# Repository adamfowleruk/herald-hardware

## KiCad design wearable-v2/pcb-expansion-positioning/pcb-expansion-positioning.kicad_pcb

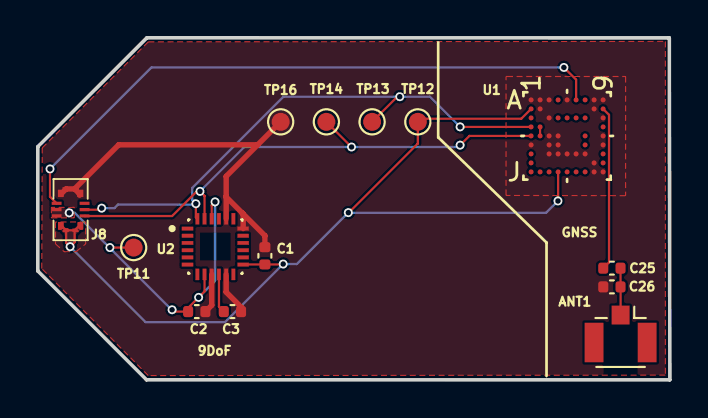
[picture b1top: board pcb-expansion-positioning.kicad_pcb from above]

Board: 2 copper layers, 35.1 x 19.0 mm, 14 parts (0 on the bottom side), 10 nets.

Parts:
ANT1: U.FL_Hirose_U.FL-R-SMT-1_Vertical
C1, C2, C3: 100nF; C_0402_1005Metric
C25: 120pF; C_0402_1005Metric
C26: Tune (~120pF); C_0402_1005Metric
J8: HERALD_V2_CONN_PLUG; HERALD_V2_CONN_PORT
TP11: VDD1; TestPoint_Pad_D1.0mm
TP12: VDD; TestPoint_Pad_D1.0mm
TP13: SDA; TestPoint_Pad_D1.0mm
TP14: SCL; TestPoint_Pad_D1.0mm
TP16: GND; TestPoint_Pad_D1.0mm
U1: MIA-M10Q-00B; LGA_M10Q-00B_UBL
U2: ICM-20948; ICM-20948-QFN40P300X300X105-24N

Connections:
/Positioning Board V1/ANT_RF: C25.1, U1.B9 (RF_IN)
/Positioning Board V1/GNSS_INT: J8.6 (INT), U1.A6 (EXTINT)
/Positioning Board V1/SCL: J8.3 (SCL), TP14.1, U1.E1 (SCL), U2.23 (SCL/SCLK)
/Positioning Board V1/SDA: J8.5 (SDA), TP13.1, U1.D1 (SDA), U2.24 (SDA/SDI)
GND: C1.2, C2.1, C3.1, C26.2, J8.8 (GND), TP16.1, U1.A1 (GND), U1.A2 (GND), U1.A3 (GND), U1.A5 (RTC_O), U1.A8 (GND), U1.A9 (GND), U1.B2 (GND), U1.B8 (GND), U1.C3 (GND), U1.C9 (GND), U1.E3 (GND), U1.E4 (GND), U1.E9 (GND), U1.F1 (GND), U1.F3 (GND), U1.F4 (GND), U1.F9 (RESERVED), U1.G3 (GND), U1.G4 (GND), U1.G5 (GND), U1.G6 (GND), U1.G7 (RESERVED), U1.H8 (GND), U1.J8 (GND), U1.J9 (GND), U2.9 (AD0/SDO), U2.11 (FSYNC), U2.18 (GND), U2.20 (RESV_20)
unnamed: ANT1.1, C25.2, C26.1
unnamed: U1.D2 (RESERVED), U1.E2 (RESERVED)
unnamed: C3.2, U2.10 (REGOUT)
VDD: C1.1, J8.1 (3V3), TP12.1, U1.B1 (VCC), U1.J4 (V_IO), U2.13 (VDD)
VDD1: C2.2, J8.2 (1V8), J8.4 (1V8), TP11.1, U2.8 (VDDIO), U2.22 (~CS)

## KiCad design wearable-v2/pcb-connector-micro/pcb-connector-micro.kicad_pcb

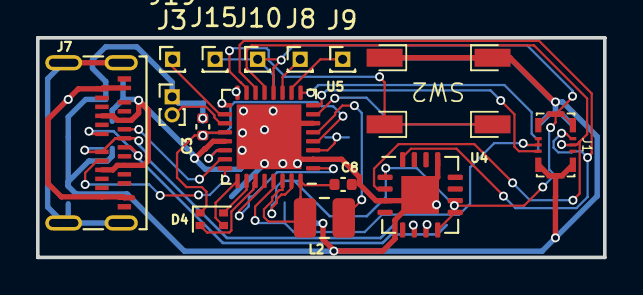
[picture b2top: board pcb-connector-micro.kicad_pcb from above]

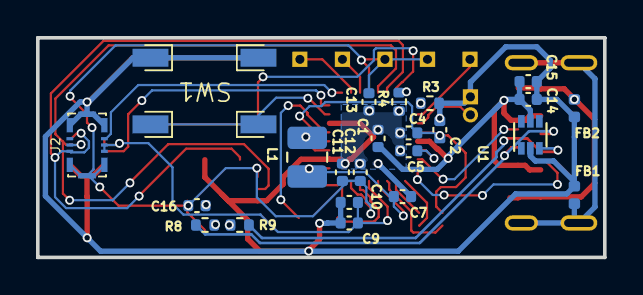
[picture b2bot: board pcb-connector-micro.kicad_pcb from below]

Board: 2 copper layers, 31.5 x 12.2 mm, 38 parts (23 on the bottom side), 33 nets.

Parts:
C1, C5: 1uF; C_0402_1005Metric
C2, C3, C4, C7, C8, C9, C10, C11, C12: 10uF; C_0402_1005Metric
C13, C16: 100nF; C_0402_1005Metric
C14: 4.7uF; C_0402_1005Metric
C15: 100nF/100V; C_0402_1005Metric
D4: LED_ARGY; LED_Kingbright_APHF1608
FB1, FB2: 120R/0.6A; L_0402_1005Metric
J1, J2: HERALD_V2_CONN_RECEPTACLE
J3, J8, J9, J10, J15: Conn_01x01_Pin; PinHeader_1x01_P1.00mm_Vertical
J7: USB_C_Receptacle_USB2.0; USB_C_Receptacle_IPxx
J19: Conn_01x02_Pin; PinHeader_1x02_P1.00mm_Vertical
L1, L2: 2.2uH; L_1008_2520Metric
R3: 4.7K; R_0402_1005Metric
R4: 499K; R_0402_1005Metric
R8, R9: 27; R_0402_1005Metric
SW1, SW2: PTS526
U1: DT1446-04V; SOT-563
U4: FT201XQ; QFN-16-1EP_4x4mm_P0.65mm_EP2.1x2.1mm
U5: nPM1300-QEAA; QFN-32-1EP_5x5mm_P0.5mm_EP3.6x3.6mm

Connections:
/Micro Connector/+BATT: J19.2, U5.19 (VBAT)
/Micro Connector/CC1: J7.A5 (CC1), U5.23 (CC1)
/Micro Connector/CC2: J7.B5 (CC2), U5.24 (CC2)
/Micro Connector/GPIO_1: J9.1, U5.10 (GPIO3)
/Micro Connector/GPIO_2: J8.1, U5.11 (GPIO4)
/Micro Connector/I3C_SCL: J1.3 (SCL), J2.3 (SCL), U4.16 (SCL), U5.14 (SCL)
/Micro Connector/I3C_SDA: J1.5 (SDA), J2.5 (SDA), U4.2 (SDA), U5.13 (SDA)
/Micro Connector/INT_1: J1.6 (INT), U5.8 (GPIO1)
/Micro Connector/INT_2: J2.6 (INT), U5.9 (GPIO2)
/Micro Connector/LED_PWR_G: D4.3 (GK), U5.25 (LED0)
/Micro Connector/LED_PWR_R: D4.2 (RK), U5.27 (LED2)
/Micro Connector/LED_PWR_Y: D4.4 (BK), U5.26 (LED1)
/Micro Connector/NTC: J3.1, U5.18 (NTC)
/Micro Connector/RST_CONN: SW1.1, SW1.2, U5.7 (GPIO0)
/Micro Connector/USB_D+: J7.A6 (D+), J7.B6 (D+), R9.1, U1.3
/Micro Connector/USB_D-: J7.A7 (D-), J7.B7 (D-), R8.2, U1.1
/Micro Connector/VBUSOUT: C5.1, U5.22 (VBUSOUT)
/Micro Connector/VCC_1V8: C9.1, C10.1, J1.2 (1V8), J1.4 (1V8), J2.2 (1V8), J2.4 (1V8), U5.29 (VOUTLDO1)
/Micro Connector/VOUT1: C7.1, L1.1, U5.1 (VOUT1), U5.28 (VINLDO1)
/Micro Connector/VOUT2: C8.1, L2.1, U5.30 (VINLDO2), U5.32 (VOUT2)
/Micro Connector/VSYS: C2.1, C3.1, C4.1, D4.1 (A), U5.4 (PVDD), U5.20 (VSYS)
Earth: FB1.1, J7.S1 (SHIELD)
GND: C1.2, C2.2, C3.2, C4.2, C5.2, C7.2, C8.2, C9.2, C10.2, C11.2, C12.2, C13.1, C14.1, C15.1, C16.2, FB1.2, FB2.2, J1.8 (GND), J2.8 (GND), J19.1, R3.2, R4.1, SW1.3, SW1.4, SW2.3, SW2.4, U1.2, U4.3 (GND), U4.13 (GND), U4.17 (GND), U5.2 (PVSS1), U5.6 (PVSS2), U5.33 (AVS)
GNDPWR: FB2.1, J7.A1 (GND), J7.A12 (GND), J7.B1 (GND), J7.B12 (GND)
unnamed: R8.1, U4.7 (USBDM)
unnamed: R9.2, U4.6 (USBDP)
unnamed: SW2.1, SW2.2, U5.15 (SHPHLD)
unnamed: L1.2, U5.3 (SW1)
unnamed: L2.2, U5.5 (SW2)
unnamed: R3.1, U5.17 (VSET1)
unnamed: R4.2, U5.16 (VSET2)
VBUS: C1.1, C14.2, C15.2, J7.A4 (VBUS), J7.A9 (VBUS), J7.B4 (VBUS), J7.B9 (VBUS), U1.5, U5.21 (VBUS)
VDD: C11.1, C12.1, C13.2, C16.1, J1.1 (3V3), J2.1 (3V3), J10.1, J15.1, U4.1 (VCCIO), U4.8 (3V3OUT), U4.9 (~RESET), U4.10 (VCC), U5.12 (VDDIO), U5.31 (VOUTLDO2)

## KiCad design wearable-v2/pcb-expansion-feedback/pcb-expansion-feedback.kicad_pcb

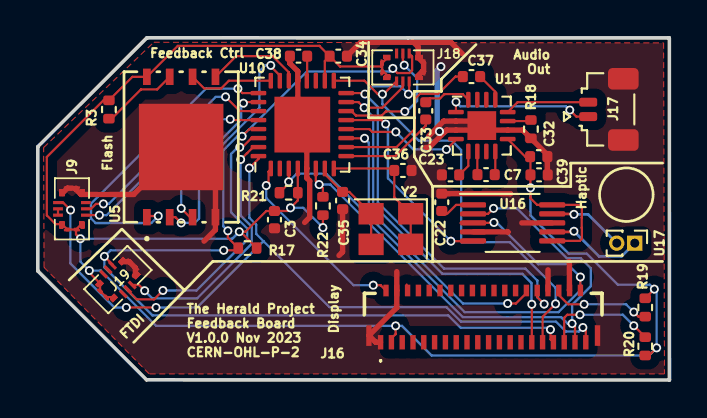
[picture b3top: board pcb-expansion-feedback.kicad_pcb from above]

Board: 2 copper layers, 35.1 x 19.0 mm, 31 parts (0 on the bottom side), 43 nets.

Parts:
BoardFeedback: Board Feedback; Board
C3, C38, C39: 100nF 0402; C_0402_1005Metric
C7, C22, C23, C32: 1uF 0402; C_0402_1005Metric
C33, C37: 2.2uF 0402; C_0402_1005Metric
C34: 10uF 0402; C_0402_1005Metric
C35, C36: 22pF 0402; C_0402_1005Metric
J9, J19: HERALD_V2_CONN_PLUG; HERALD_V2_CONN_PORT
J16: EA_WF030-39S; EAWF03039S
J17: JST_AUDIO_OUT; JST_SUR_SM02B-SURS-TF_1x02-1MP_P0.80mm_Horizontal
J18: HERALD_V2_CONN_PLUG_ARMSWD; HERALD_V2_CONN_PORT
R3: 10k; R_0402_1005Metric
R17, R21, R22: 1k 0402; R_0402_1005Metric
R18: 49.9k 0402; R_0402_1005Metric
R19, R20: 10k 0402; R_0402_1005Metric
U5: MX25R6435FZNIL0; 8-WSON_MAC
U10: ATmega328PB-M; QFN-32-1EP_5x5mm_P0.5mm_EP3.1x3.1mm
U13: TPA6139A2RGTR; TQFN-16-1EP_3x3mm_P0.5mm_EP1.6x1.6mm
U16: DRV2605LDGSR; VSSOP-10_3x3mm_P0.5mm
U17: VG0832013D; PinHeader_1x02_P1.00mm_Vertical
Y2: 8Mhz; Crystal_SMD_3225-4Pin_3.2x2.5mm

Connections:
/ Display Board V1/DISP_CSX: J16.28, U10.11 (PD7)
/ Display Board V1/DISP_DCX: J16.31, J18.3 (SCL), U10.17 (PB5)
/ Display Board V1/DISP_IM1+IM2: J16.34, R19.2
/ Display Board V1/DISP_IM3: J16.35, R20.2
/ Display Board V1/DISP_SDA: J16.29, J18.5 (SDA), U10.15 (PB3)
/ Display Board V1/DISP_SDO: J16.30, J18.7 (SDO), U10.16 (PB4)
/ Display Board V1/FB_AUDIO_PWM_LEFT: C33.2, U10.9 (PD5)
/ Display Board V1/FB_AUDIO_PWM_RIGHT: C37.1, U10.10 (PD6)
/ Display Board V1/FB_AUDIO_SEL: U10.12 (PB0), U13.4 (MUTE)
/ Display Board V1/FB_AVR_RESET: J16.33, J18.6 (RST), J19.6 (INT), R17.1, U10.29 (~RESET/PC6)
/ Display Board V1/FB_FLASH_RST: R3.2, U5.7 (~RESET/SIO3)
/ Display Board V1/FB_FLASH_SEL: U5.1 (~CS), U10.25 (PC2)
/ Display Board V1/FB_FLASH_WP: U5.3 (~WP/SIO2), U10.26 (PC3)
/ Display Board V1/FB_INT: J9.6 (INT), J16.39, U10.32 (PD2)
/ Display Board V1/FB_LED_PWM: J16.2, U10.1 (PD3)
/ Display Board V1/FB_LRA+: U16.7 (OUT+), U17.1 (LRA+)
/ Display Board V1/FB_LRA-: U16.9 (OUT-), U17.2 (LRA-)
/ Display Board V1/FB_MISO1: U5.2 (SO/SIO1), U10.23 (PC0)
/ Display Board V1/FB_MOSI1: U5.5 (SI/SIO0), U10.22 (PE3)
/ Display Board V1/FB_SCK1: U5.6 (SCLK), U10.24 (PC1)
/ Display Board V1/FB_SCL: J16.37, R22.2, U10.6 (PE1), U16.2 (SCL)
/ Display Board V1/FB_SDA: J16.38, R21.2, U10.3 (PE0), U16.3 (SDA)
/ Display Board V1/FB_SPEAKER_OUT_LEFT: J17.1, U13.1 (OUT_L)
/ Display Board V1/FB_SPEAKER_OUT_RIGHT: J17.2, U13.12 (OUT_R)
/ Display Board V1/FB_SS0: J18.4 (SEL), U10.14 (PB2)
/ Display Board V1/FB_TWI_RX: J19.5 (SDA), U10.30 (PD0)
/ Display Board V1/FB_TWI_TX: J19.7 (GPIO), U10.31 (PD1)
/ Display Board V1/FB_VIBRATE_EN: U10.13 (PB1), U16.5 (EN)
/ Display Board V1/I3C_SCL: J9.3 (SCL), U10.28 (PC5)
/ Display Board V1/I3C_SDA: J9.5 (SDA), U10.27 (PC4)
/ Display Board V1/VCC_1V8: J9.2 (1V8), J9.4 (1V8)
GND: C3.1, C22.1, C23.2, C32.2, C34.2, C35.1, C36.1, C38.1, C39.2, J9.8 (GND), J16.1, J16.4, J16.32, J16.36, J16.MP1, J16.MP2, J17.MP, J18.8 (GND), J19.8 (GND), R18.2, U5.4 (GND), U5.9, U10.5 (GND), U10.21 (GND), U10.33 (GND), U13.2 (GND), U13.3 (GND), U13.10 (GND), U13.17 (GND), U16.4 (IN/TRIG), U16.8 (GND)
unnamed: C38.2, U10.20 (AREF)
unnamed: C35.2, U10.7 (XTAL1/PB6), Y2.2, Y2.3
unnamed: C36.2, U10.8 (XTAL2/PB7), Y2.1, Y2.4
unnamed: C7.2, U13.6 (CN)
unnamed: C7.1, U13.8 (CP)
unnamed: R18.1, U13.11 (GAIN)
unnamed: C33.1, U13.16 (IN_L)
unnamed: C37.2, U13.13 (IN_R)
unnamed: C23.1, U13.5 (VSS)
unnamed: C22.2, U16.1 (REG)
VDD: C3.2, C32.1, C34.1, C39.1, J9.1 (3V3), J16.3, J18.1 (3V3), J19.1 (3V3), R3.1, R17.2, R19.1, R20.1, R21.1, R22.1, U5.8 (VCC), U10.4 (VCC), U10.18 (AVCC), U13.9 (VDD), U16.6 (VDD/NC), U16.10 (VDD)

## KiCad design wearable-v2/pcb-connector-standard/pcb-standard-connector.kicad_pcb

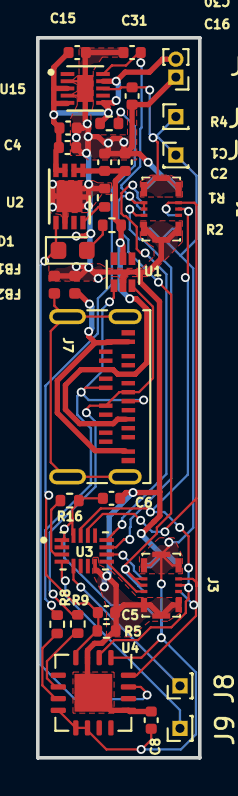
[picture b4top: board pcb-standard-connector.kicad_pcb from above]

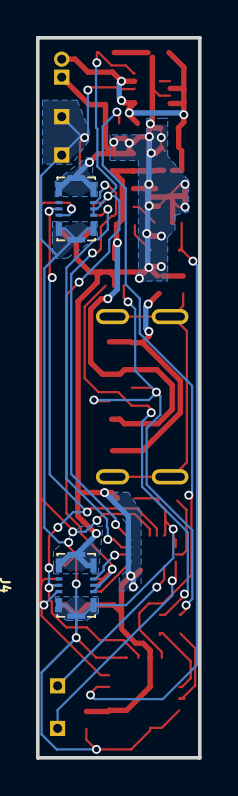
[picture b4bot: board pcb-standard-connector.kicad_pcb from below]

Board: 2 copper layers, 9.0 x 40.0 mm, 35 parts (2 on the bottom side), 24 nets.

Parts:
C1, C4, C6: 4.7uF; C_0402_1005Metric
C2: 100nF/100V; C_0402_1005Metric
C5: 10nF; C_0402_1005Metric
C8: 100nF; C_0402_1005Metric
C15, C16, C30, C31: 1uF; C_0402_1005Metric
D1: CHSTAT; LED_0603_1608Metric
FB1, FB2: 120R/0.6A; L_0402_1005Metric
J1, J2, J3, J4: HERALD_V2_CONN_RECEPTACLE
J7: USB_C_Receptacle_USB2.0; USB_C_Receptacle_IPxx
J8, J9, J10, J15: Conn_01x01_Pin; PinHeader_1x01_P1.00mm_Vertical
J18: Conn_01x02_Pin; PinHeader_1x02_P1.00mm_Vertical
R1, R16: 10k; R_0402_1005Metric
R2: 5.6k; R_0402_1005Metric
R4: 6.8M; R_0402_1005Metric
R5: 10M; R_0402_1005Metric
R8, R9: 27; R_0402_1005Metric
U1: DT1446-04V; SOT-563
U2: MCP73831/2-2MC; DFN-8-1EP_3x2mm_P0.5mm_EP1.75x1.45mm
U3: TCA6408A; QFN40P180X260X55-16N
U4: FT201XQ; QFN-16-1EP_4x4mm_P0.65mm_EP2.1x2.1mm
U15: TLV751; SON40P200X200X80-11N

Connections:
+1V8: C31.2, J1.2 (1V8), J1.4 (1V8), J2.2 (1V8), J2.4 (1V8), J3.2 (1V8), J3.4 (1V8), J4.2 (1V8), J4.4 (1V8), U15.10 (OUT1)
+BATT: C4.2, C15.2, C16.2, J18.2, R4.1, U2.3 (VBAT), U2.4 (VBAT), U15.3 (EN1), U15.5 (EN2), U15.6 (IN2), U15.9 (IN1)
/Standard Connector/BT_STAT: C5.1, R4.2, R5.1, U4.4 (CBUS4)
/Standard Connector/CH_STAT: D1.1 (K), U2.5 (STAT), U4.15 (CBUS5)
/Standard Connector/GPIO_1: J9.1, U3.4 (P0)
/Standard Connector/GPIO_2: J8.1, U3.5 (P1)
/Standard Connector/I3C_SCL: J1.3 (SCL), J2.3 (SCL), J3.3 (SCL), J4.3 (SCL), U3.14 (SCL), U4.16 (SCL)
/Standard Connector/I3C_SDA: J1.5 (SDA), J2.5 (SDA), J3.5 (SDA), J4.5 (SDA), U3.15 (SDA), U4.2 (SDA)
/Standard Connector/INT_1: J1.6 (INT), U3.11 (P6)
/Standard Connector/INT_2: J2.6 (INT), U3.12 (P7)
/Standard Connector/INT_3: J3.6 (INT), U3.9 (P4)
/Standard Connector/INT_4: J4.6 (INT), U3.10 (P5)
/Standard Connector/RST_CONN: R16.2, U3.3 (RST)
/Standard Connector/USB_D+: J7.A6 (D+), J7.B6 (D+), R9.1, U1.3
/Standard Connector/USB_D-: J7.A7 (D-), J7.B7 (D-), R8.2, U1.1
Earth: FB1.1, J7.S1 (SHIELD)
GND: C1.1, C2.1, C4.1, C5.2, C6.2, C8.2, C15.1, C16.1, C30.1, C31.1, FB1.2, FB2.2, J1.8 (GND), J2.8 (GND), J3.8 (GND), J4.8 (GND), J18.1, R1.1, R5.2, U1.2, U2.6 (VSS), U2.9, U3.8 (GND), U4.3 (GND), U4.13 (GND), U4.17 (GND), U15.2 (GND), U15.4 (GND), U15.11
GNDPWR: FB2.1, J7.A1 (GND), J7.A12 (GND), J7.B1 (GND), J7.B12 (GND)
unnamed: D1.2 (A), R2.1
unnamed: R1.2, U2.8 (PROG)
unnamed: R8.1, U4.7 (USBDM)
unnamed: R9.2, U4.6 (USBDP)
VBUS: C1.2, C2.2, J7.A4 (VBUS), J7.A9 (VBUS), J7.B4 (VBUS), J7.B9 (VBUS), R2.2, U1.5, U2.1 (VDD), U2.2 (VDD)
VDD: C6.1, C8.1, C30.2, J1.1 (3V3), J2.1 (3V3), J3.1 (3V3), J4.1 (3V3), J10.1, J15.1, R16.1, U3.1 (VCCI), U3.2 (ADDR), U3.16 (VCCP), U4.1 (VCCIO), U4.8 (3V3OUT), U4.9 (~RESET), U4.10 (VCC), U15.8 (OUT2)

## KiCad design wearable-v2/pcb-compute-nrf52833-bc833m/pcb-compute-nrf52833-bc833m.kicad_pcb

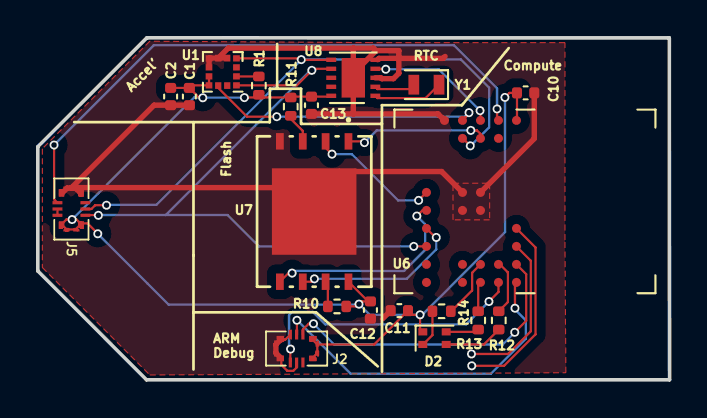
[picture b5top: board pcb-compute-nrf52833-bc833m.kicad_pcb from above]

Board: 2 copper layers, 35.1 x 19.0 mm, 21 parts (0 on the bottom side), 26 nets.

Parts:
C1, C11: 10uF; C_0402_1005Metric
C2, C12, C13: 100nF; C_0402_1005Metric
C10: 4.7uF; C_0402_1005Metric
ComputeBC833M: Board Compute BC833M; Board
D2: LED_ARBG; LED_Kingbright_APHF1608
J2: HERALD_V2_CONN_PLUG_ARMSWD; HERALD_V2_CONN_PORT
J5: HERALD_V2_CONN_PLUG; HERALD_V2_CONN_PORT
R1, R10, R11: 10k; R_0402_1005Metric
R12: 0; R_0402_1005Metric
R13: 3.9k; R_0402_1005Metric
R14: 1k; R_0402_1005Metric
U1: LIS2DE12; LGA-12_2x2mm_P0.5mm
U6: BC833; Fanstel_BC833x
U7: MX25R6435F; 8-WSON_MAC
U8: PCF85063ATL; DFN-10-1EP_2.6x2.6mm_P0.5mm_EP1.25x2.15mm
Y1: 32.768kHz; Crystal_SMD_2012-2Pin_2.0x1.2mm

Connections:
/Compute BC833M/ACC_INT2: U1.11 (INT2), U6.4 (P0.28/AIN4)
/Compute BC833M/EXT_INT1: J5.6 (INT), U6.2 (P0.03/AIN1)
/Compute BC833M/FLASH_CS: U6.7 (P0.30/AIN6), U7.1 (~CS)
/Compute BC833M/FLASH_RST: R10.2, U7.7 (~RESET/SIO3)
/Compute BC833M/FLASH_WP: R11.2, U7.3 (~WP/SIO2)
/Compute BC833M/LED_B: R12.1, U6.21 (P0.20)
/Compute BC833M/LED_G: R13.1, U6.16 (P0.15)
/Compute BC833M/LED_R: R14.1, U6.20 (P0.17)
/Compute BC833M/MISO: U6.9 (P0.04/AIN2), U7.2 (SO/SIO1)
/Compute BC833M/MOSI: U6.10 (P0.05/AIN3), U7.5 (SI/SIO0)
/Compute BC833M/RESETn: J2.6 (RST), U6.17 (~RESET/P0.18)
/Compute BC833M/RTC_INT: U6.3 (P0.02/AIN0), U8.4 (~INT)
/Compute BC833M/SCL: J5.3 (SCL), U1.1 (SCL/SPC), U6.12 (P0.11), U8.7 (SCL)
/Compute BC833M/SCLK: U6.11 (P1.09), U7.6 (SCLK)
/Compute BC833M/SDA: J5.5 (SDA), U1.4 (SDA/SDI), U6.8 (P0.31/AIN7), U8.6 (SDA)
/Compute BC833M/SWDCLK: J2.3 (SCL), U6.22 (SWDCLK)
/Compute BC833M/SWDIO: J2.5 (SDA), U6.18 (SWDIO)
/Compute BC833M/VCC_1V8: J5.2 (1V8), J5.4 (1V8)
GND: C1.2, C2.2, C10.2, C11.2, C12.1, C13.2, J2.4 (SEL), J2.7 (SDO), J2.8 (GND), J5.8 (GND), U1.5 (RES), U1.6 (GND), U1.7 (GND), U1.8 (GND), U6.5 (GND), U6.25 (GND), U6.26 (GND), U6.27 (GND), U6.28 (GND), U7.4 (GND), U7.9, U8.3 (CLKOE), U8.5 (VSS), U8.EP
unnamed: D2.3 (BK), R12.2
unnamed: D2.4 (GK), R13.2
unnamed: D2.2 (RK), R14.2
unnamed: R1.2, U1.2 (~CS)
unnamed: U8.1 (OSCI), Y1.1
unnamed: U8.2 (OSCO), Y1.2
VDD: C1.1, C2.1, C10.1, C11.1, C12.2, C13.1, D2.1 (A), J2.1 (3V3), J5.1 (3V3), R1.1, R10.1, R11.1, U1.9 (Vdd), U1.10 (Vdd_IO), U6.1 (VDD), U7.8 (VCC), U8.10 (VDD)

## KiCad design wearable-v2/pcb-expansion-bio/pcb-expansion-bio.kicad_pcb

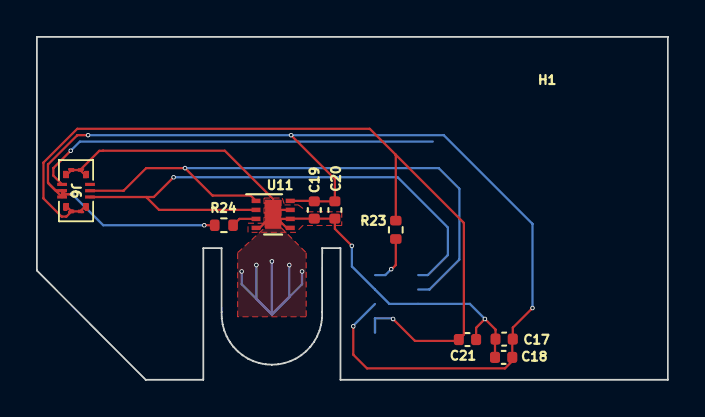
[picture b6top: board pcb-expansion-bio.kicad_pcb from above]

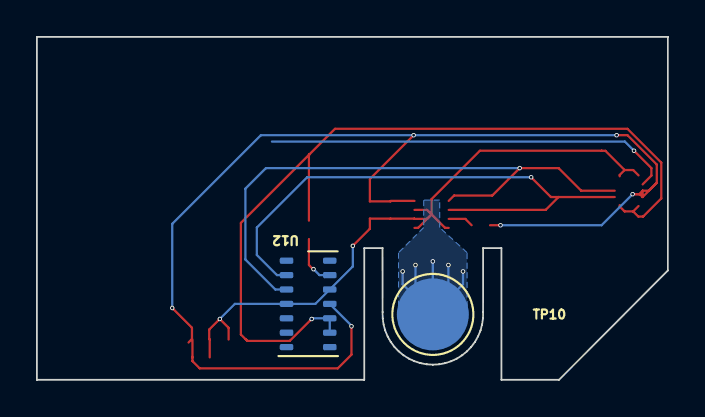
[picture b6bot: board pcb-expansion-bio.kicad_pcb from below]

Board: 2 copper layers, 35.1 x 19.0 mm, 13 parts (2 on the bottom side), 7 nets.

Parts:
BoardBio: Board Bio; Board
C17, C21: 10uF; C_0402_1005Metric
C18, C19: 100nF; C_0402_1005Metric
C20: 4.7uF; C_0402_1005Metric
H1: ThermalSlot; MillSlot_8.0x1.0mm
J6: HERALD_V2_CONN_PLUG; HERALD_V2_CONN_PORT
R23, R24: 1k 0402; R_0402_1005Metric
TP10: ThPad; TestPoint_Pad_D4.0mm
U11: TMP1075; WSON-8-1EP_2x2mm_P0.5mm_EP0.9x1.6mm
U12: MAX30102; Maxim_OLGA-14_3.3x5.6mm_P0.8mm

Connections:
+1V8: C17.1, C18.1, C19.2, C20.2, J6.2 (1V8), J6.4 (1V8), R24.1, U11.8 (+Vs), U12.11 (VDD)
/Bio Board V1/BIO_INT: R23.2, U12.13 (~INT)
/Bio Board V1/SCL: J6.3 (SCL), U11.2 (SCL), U12.2 (SCL)
/Bio Board V1/SDA: J6.5 (SDA), U11.1 (SDA), U12.3 (SDA)
/Bio Board V1/TMP_INT: R24.2, U11.3 (ALRT)
GND: C17.2, C18.2, C19.1, C20.1, C21.2, J6.8 (GND), TP10.1, U11.4 (GND), U11.5 (A2), U11.6 (A1), U11.7 (A0), U11.9 (EP), U12.4 (PGND), U12.12 (GND)
Vdrive: C21.1, J6.1 (3V3), R23.1, U12.9 (VLED+), U12.10 (VLED+)

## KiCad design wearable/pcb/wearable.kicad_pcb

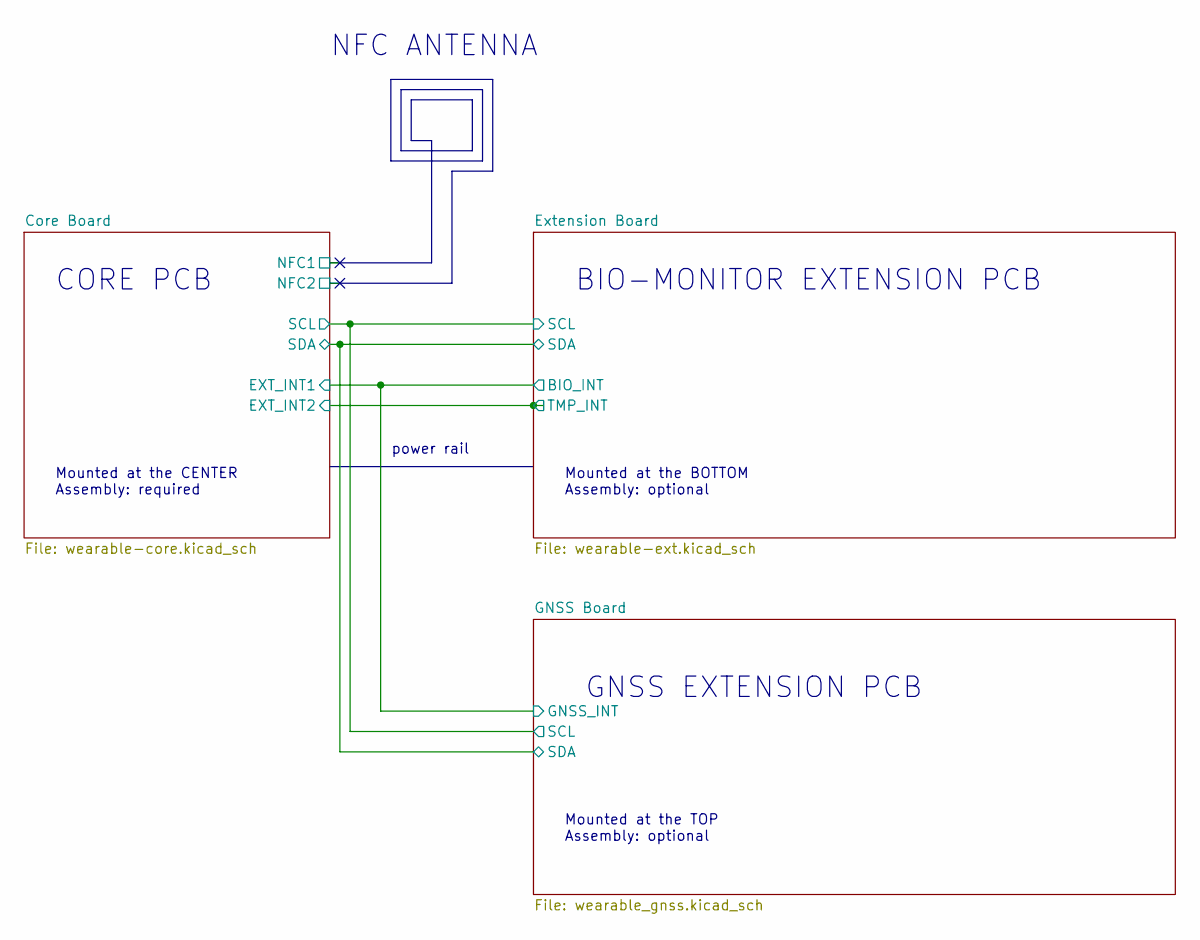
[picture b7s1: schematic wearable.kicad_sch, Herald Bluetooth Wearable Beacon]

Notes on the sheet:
NFC ANTENNA
Mounted at the CENTER Assembly: required
Mounted at the BOTTOM Assembly: optional
CORE PCB
GNSS EXTENSION PCB
power rail
Mounted at the TOP Assembly: optional
BIO-MONITOR EXTENSION PCB

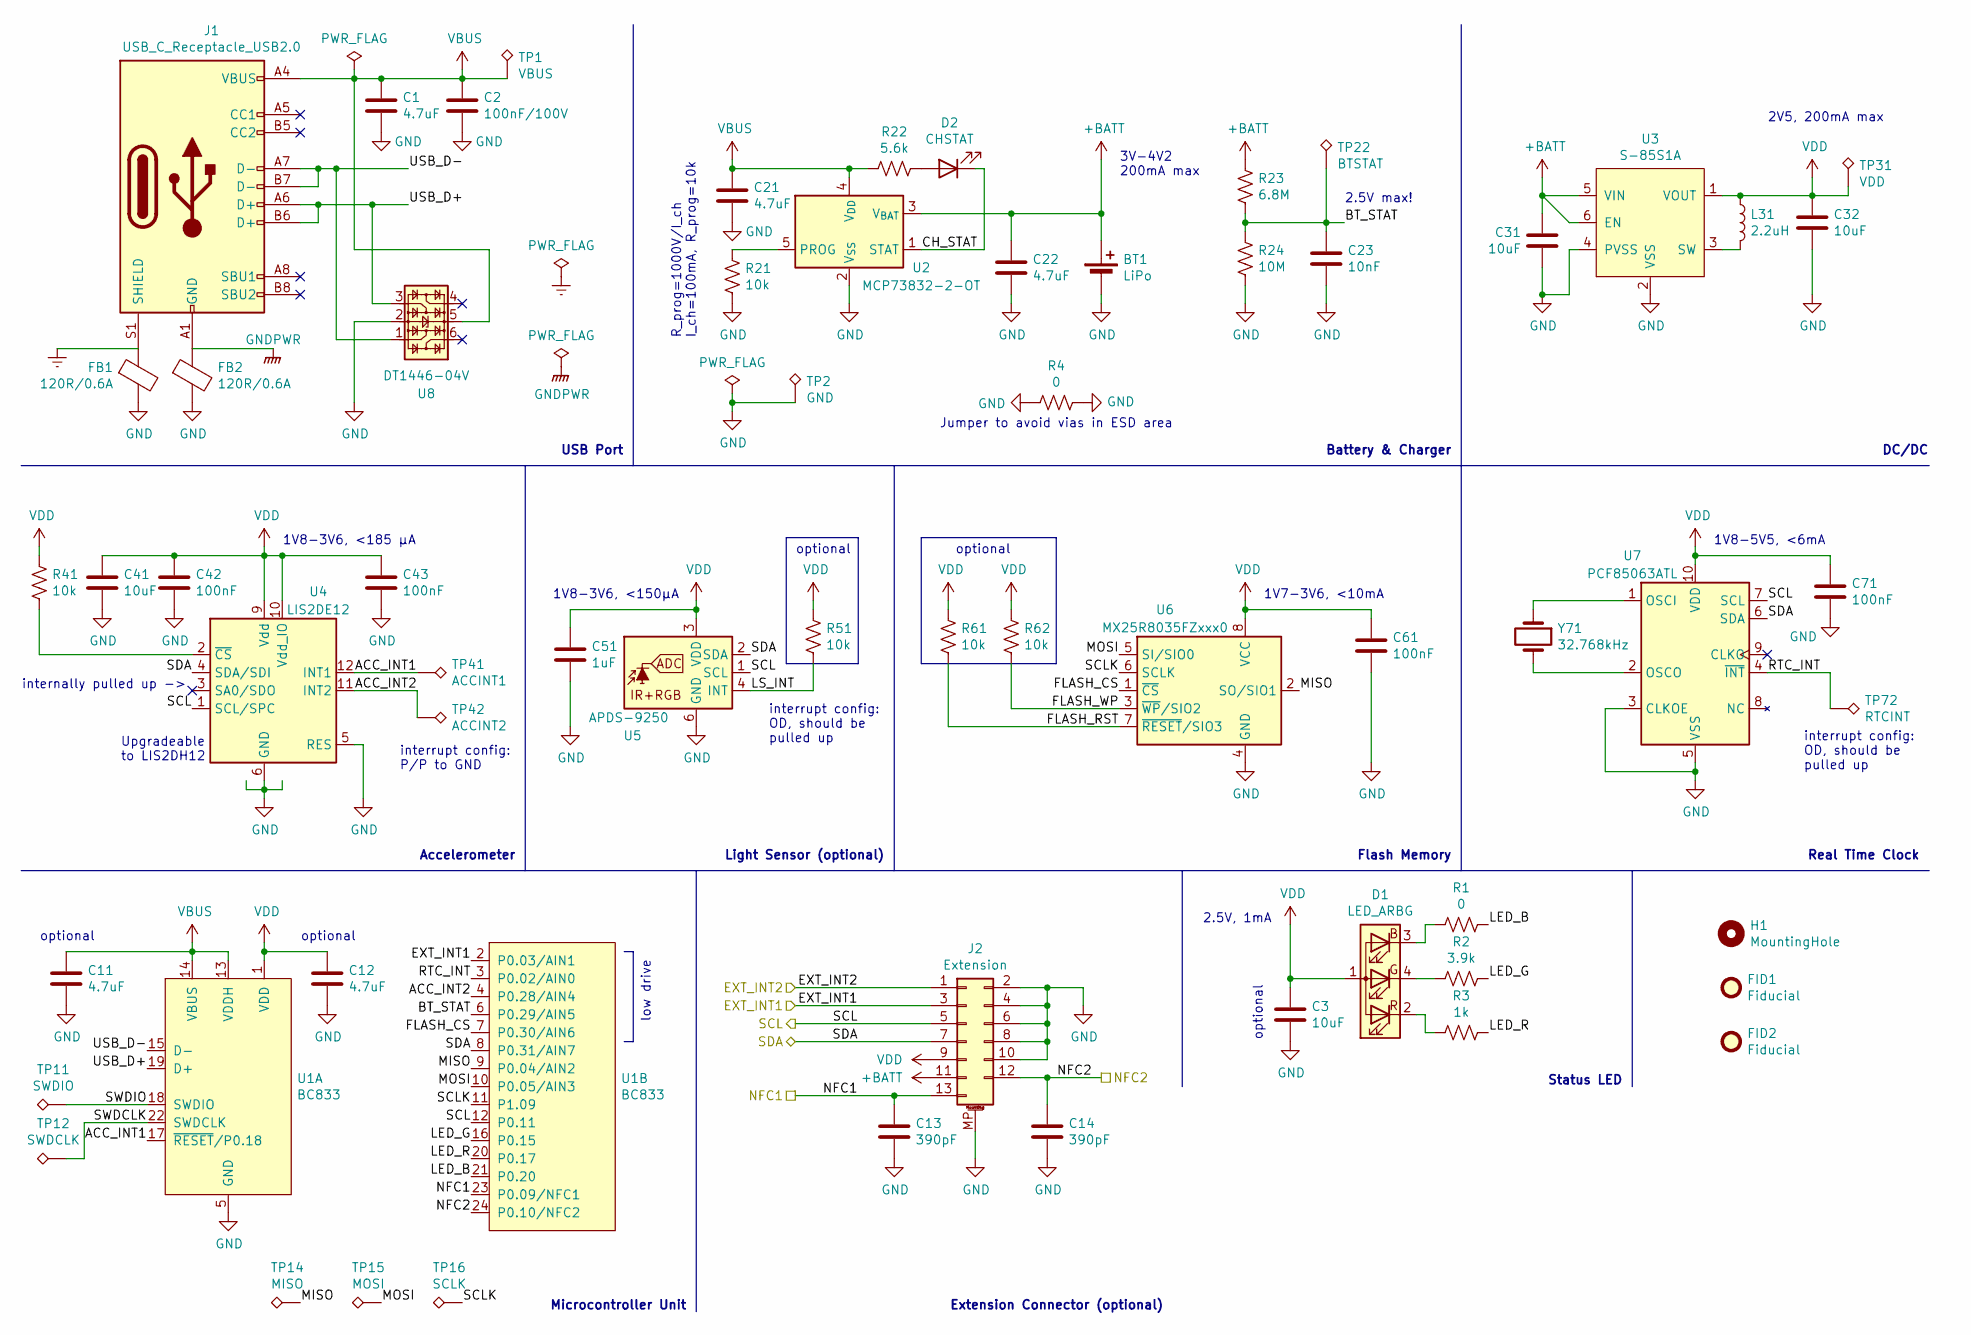
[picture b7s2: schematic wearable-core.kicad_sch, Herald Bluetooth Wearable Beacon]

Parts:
BT1: LiPo; Herald_Battery_Solder_Pads; MPN LI401225
C1, C11, C12, C21, C22: 4.7uF; C_0402_1005Metric; MPN 0402YD475MAT2A
C2: 100nF/100V; C_0402_1005Metric; MPN GRM155R62A104ME14D
C3, C31, C32, C41: 10uF; C_0402_1005Metric; MPN GRM155R60J106ME15D
C13, C14: 390pF; C_0402_1005Metric; MPN GCM1555C1H391FA16D
C23: 10nF; C_0402_1005Metric; MPN C0402C103K4RAC7411
C42, C43, C61, C71: 100nF; C_0402_1005Metric; MPN GRM155R71E104KE14D
C51: 1uF; C_0402_1005Metric; MPN GRM155R61C105KA12D
D1: LED_ARBG; LED_Kingbright_APHF1608; MPN APHF1608LSEEQBDZGKC
D2: CHSTAT; LED_0603_1608Metric; MPN KO DELLS1.22-KHLI-24
FB1, FB2: 120R/0.6A; L_0402_1005Metric; MPN MFBM1V1005-121-R
FID1, FID2: Fiducial; Fiducial_0.75mm_Mask1.5mm
H1: MountingHole; MountingHole_2mm
J1: USB_C_Receptacle_USB2.0; USB_C_Receptacle_IPxx; MPN 124018802112A
J2: Extension; TE_1-2328724-3_2Rows_13Pins_P0.3mm_Horizontal; MPN 1-2328724-3
L31: 2.2uH; L_0603_1608Metric; MPN MBKK1608T2R2M
R1: 0; R_0402_1005Metric; MPN RC0402FR-070RL
R2: 3.9k; R_0402_1005Metric; MPN RC0402FR-073K9L
R3: 1k; R_0402_1005Metric; MPN RC0402FR-071KL
R4: 0; R_0603_1608Metric; MPN CRCW06030000Z0EAC
R21, R41, R51, R61, R62: 10k; R_0402_1005Metric; MPN CRCW040210K0FKEDC
R22: 5.6k; R_0402_1005Metric; MPN RC0402FR-075R6L
R23: 6.8M; R_0402_1005Metric; MPN RK73H1ETTP6804F
R24: 10M; R_0402_1005Metric; MPN RK73H1ETTP1005F
TP1: VBUS; TestPoint_Pad_D1.0mm
TP2: GND; TestPoint_Pad_D1.0mm
TP11: SWDIO; TestPoint_Pad_D1.0mm
TP12: SWDCLK; TestPoint_Pad_D1.0mm
TP14: MISO; TestPoint_Pad_D1.0mm
TP15: MOSI; TestPoint_Pad_D1.0mm
TP16: SCLK; TestPoint_Pad_D1.0mm
TP22: BTSTAT; TestPoint_Pad_D1.0mm
TP31: VDD; TestPoint_Pad_D1.0mm
TP41: ACCINT1; TestPoint_Pad_D1.0mm
TP42: ACCINT2; TestPoint_Pad_D1.0mm
TP72: RTCINT; TestPoint_Pad_D1.0mm
U1: BC833; Fanstel_BC833x; MPN BC833M
U2: MCP73832-2-OT; SOT-23-5; MPN MCP73832T-2ACI/OT
U3: S-85S1A; SNT-6A; MPN S-85S1AB25-I6T1U
U4: LIS2DE12; LGA-12_2x2mm_P0.5mm; MPN LIS2DE12TR
U5: APDS-9250; Broadcom_DFN-6_2x2mm_P0.65mm; MPN APDS-9250
U6: MX25R8035FZxxx0; USON-8-1EP_2x3mm_P0.5mm_EP0.25x1.65mm; MPN MX25R8035FZUIL0
U7: PCF85063ATL; DFN-10-1EP_2.6x2.6mm_P0.5mm_EP1.25x2.15mm; MPN PCF85063ATL/1,118
U8: DT1446-04V; SOT-563; MPN DT1446-04V-7
Y71: 32.768kHz; Crystal_SMD_2012-2Pin_2.0x1.2mm; MPN RT2012-32.768-7-TR

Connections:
+BATT: BT1.1 (+), C22.2, C31.1, J2.11, R23.1, U2.3 (V_{BAT}), U3.5 (VIN), U3.6 (EN)
/Core Board/ACC_INT1: TP41.1, U1.17 (~RESET/P0.18), U4.12 (INT1)
/Core Board/ACC_INT2: TP42.1, U1.4 (P0.28/AIN4), U4.11 (INT2)
/Core Board/BT_STAT: C23.1, R23.2, R24.1, TP22.1, U1.6 (P0.29/AIN5)
/Core Board/CH_STAT: D2.1 (K), U2.1 (STAT)
/Core Board/EXT_INT1: J2.3, U1.2 (P0.03/AIN1); also elsewhere on the board
/Core Board/EXT_INT2: J2.1; also elsewhere on the board
/Core Board/FLASH_CS: U1.7 (P0.30/AIN6), U6.1 (~CS)
/Core Board/FLASH_RST: R61.2, U6.7 (~RESET/SIO3)
/Core Board/FLASH_WP: R62.2, U6.3 (~WP/SIO2)
/Core Board/LED_B: R1.1, U1.21 (P0.20)
/Core Board/LED_G: R2.1, U1.16 (P0.15)
/Core Board/LED_R: R3.1, U1.20 (P0.17)
/Core Board/LS_INT: R51.2, U5.4 (INT)
/Core Board/MISO: TP14.1, U1.9 (P0.04/AIN2), U6.2 (SO/SIO1)
/Core Board/MOSI: TP15.1, U1.10 (P0.05/AIN3), U6.5 (SI/SIO0)
/Core Board/NFC1: C13.1, J2.13, U1.23 (P0.09/NFC1)
/Core Board/NFC2: C14.1, J2.12, U1.24 (P0.10/NFC2)
/Core Board/RTC_INT: TP72.1, U1.3 (P0.02/AIN0), U7.4 (~INT)
/Core Board/SCL: J2.5, U1.12 (P0.11), U4.1 (SCL/SPC), U5.1 (SCL), U7.7 (SCL); also elsewhere on the board
/Core Board/SCLK: TP16.1, U1.11 (P1.09), U6.6 (SCLK)
/Core Board/SDA: J2.7, U1.8 (P0.31/AIN7), U4.4 (SDA/SDI), U5.2 (SDA), U7.6 (SDA); also elsewhere on the board
/Core Board/SWDCLK: TP12.1, U1.22 (SWDCLK)
/Core Board/SWDIO: TP11.1, U1.18 (SWDIO)
/Core Board/USB_D+: J1.A6 (D+), J1.B6 (D+), U1.19 (D+), U8.3
/Core Board/USB_D-: J1.A7 (D-), J1.B7 (D-), U1.15 (D-), U8.1
Earth: FB1.1, J1.S1 (SHIELD)
GND: BT1.2 (-), C1.1, C2.1, C3.2, C11.2, C12.2, C13.2, C14.2, C21.1, C22.1, C23.2, C31.2, C32.2, C41.2, C42.2, C43.2, C51.2, C61.1, C71.2, FB1.2, FB2.2, J2.2, J2.4, J2.6, J2.8, J2.10, J2.MP (MountPin), R4.1, R4.2, R21.2, R24.2, TP2.1, U1.5 (GND), U1.25 (GND), U1.26 (GND), U1.27 (GND), U1.28 (GND), U2.2 (V_{SS}), U3.2 (VSS), U3.4 (PVSS), U4.5 (RES), U4.6 (GND), U4.7 (GND), U4.8 (GND), U5.6 (GND), U6.4 (GND), U6.EP (GND), U7.3 (CLKOE), U7.5 (VSS), U8.2
GNDPWR: FB2.1, J1.A1 (GND), J1.A12 (GND), J1.B1 (GND), J1.B12 (GND)
unnamed: D1.3 (BK), R1.2
unnamed: D1.4 (GK), R2.2
unnamed: D1.2 (RK), R3.2
unnamed: D2.2 (A), R22.1
unnamed: R21.1, U2.5 (PROG)
unnamed: L31.2, U3.3 (SW)
unnamed: R41.2, U4.2 (~CS)
unnamed: U7.1 (OSCI), Y71.1
unnamed: U7.2 (OSCO), Y71.2
VBUS: C1.2, C2.2, C11.1, C21.2, J1.A4 (VBUS), J1.A9 (VBUS), J1.B4 (VBUS), J1.B9 (VBUS), R22.2, TP1.1, U1.13 (VDDH), U1.14 (VBUS), U2.4 (V_{DD}), U8.5
VDD: C3.1, C12.1, C32.1, C41.1, C42.1, C43.1, C51.1, C61.2, C71.1, D1.1 (A), J2.9, L31.1, R41.1, R51.1, R61.1, R62.1, TP31.1, U1.1 (VDD), U3.1 (VOUT), U4.9 (Vdd), U4.10 (Vdd_IO), U5.3 (VDD), U6.8 (VCC), U7.10 (VDD)

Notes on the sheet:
Microcontroller Unit
2.5V, 1mA
internally pulled up ->
Upgradeable to LIS2DH12
interrupt config: OD, should be pulled up
DC/DC
Accelerometer
low drive
interrupt config: P/P to GND
optional
Real Time Clock
1V8-3V6, <185 µA
Jumper to avoid vias in ESD area
USB Port
1V8-3V6, <150µA
Light Sensor (optional)
R_prog=1000V/I_ch I_ch=100mA, R_prog=10k
2.5V max!
Flash Memory
3V-4V2 200mA max
1V7-3V6, <10mA
Status LED
2V5, 200mA max
Extension Connector (optional)
1V8-5V5, <6mA
Battery & Charger

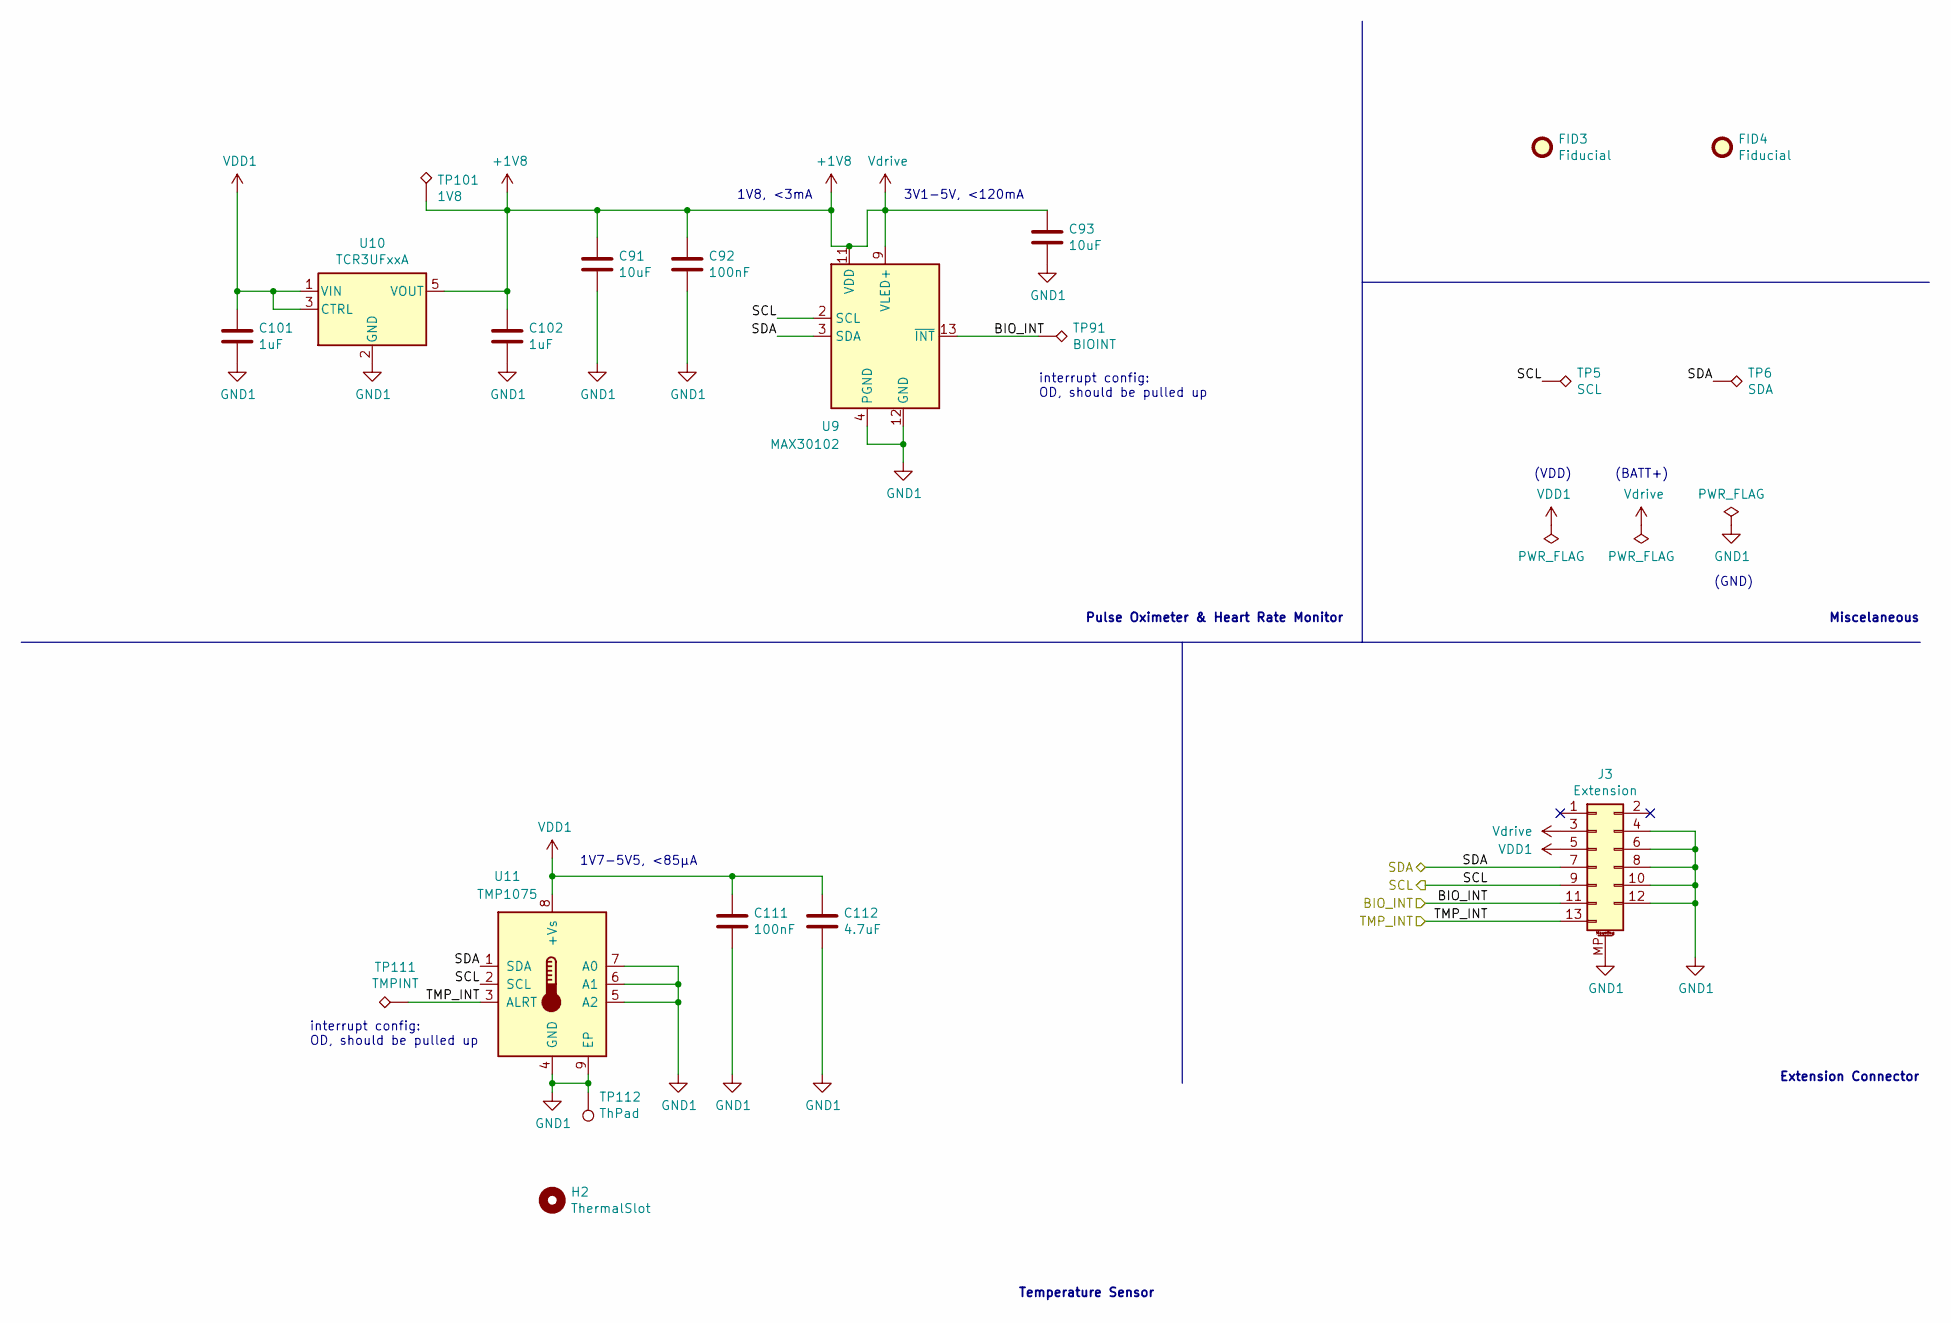
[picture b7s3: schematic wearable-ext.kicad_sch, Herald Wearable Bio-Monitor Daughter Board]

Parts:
C91, C93: 10uF; C_0402_1005Metric; MPN GRM155R60J106ME15D
C92, C111: 100nF; C_0402_1005Metric; MPN GRM155R71E104KE14D
C101, C102: 1uF; C_0402_1005Metric; MPN GRM155R61C105KA12D
C112: 4.7uF; C_0402_1005Metric; MPN 0402YD475MAT2A
FID3, FID4: Fiducial; Fiducial_0.75mm_Mask1.5mm
H2: ThermalSlot; MillSlot_8.0x1.0mm
J3: Extension; TE_1-2328724-3_2Rows_13Pins_P0.3mm_Horizontal; MPN 1-2328724-3
TP5: SCL; TestPoint_Pad_D1.0mm
TP6: SDA; TestPoint_Pad_D1.0mm
TP91: BIOINT; TestPoint_Pad_D1.0mm
TP101: 1V8; TestPoint_Pad_D1.0mm
TP111: TMPINT; TestPoint_Pad_D1.0mm
TP112: ThPad; TestPoint_Pad_D4.0mm
U9: MAX30102; Maxim_OLGA-14_3.3x5.6mm_P0.8mm; MPN MAX30102EFD+T
U10: TCR3UFxxA; SOT-23-5; MPN TCR3UF18A
U11: TMP1075; WSON-8-1EP_2x2mm_P0.5mm_EP0.9x1.6mm; MPN TMP1075DSGT

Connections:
+1V8: C91.1, C92.1, C93.1, C102.1, J3.3, TP101.1, U9.9 (VLED+), U9.10 (VLED+), U9.11 (VDD), U10.5 (VOUT); also elsewhere on the board
/Core Board/EXT_INT1: J3.11, TP91.1, U9.13 (~INT); also elsewhere on the board
/Core Board/EXT_INT2: J3.13, TP111.1, U11.3 (ALRT); also elsewhere on the board
/Core Board/SCL: J3.9, TP5.1, U9.2 (SCL), U11.2 (SCL); also elsewhere on the board
/Core Board/SDA: J3.7, TP6.1, U9.3 (SDA), U11.1 (SDA); also elsewhere on the board
GND1: C91.2, C92.2, C93.2, C101.2, C102.2, C111.1, C112.1, J3.4, J3.6, J3.8, J3.10, J3.12, J3.MP (MountPin), TP112.1, U9.4 (PGND), U9.12 (GND), U10.2 (GND), U11.4 (GND), U11.5 (A2), U11.6 (A1), U11.7 (A0), U11.9 (EP); also elsewhere on the board
VDD1: C101.1, C111.2, C112.2, J3.5, U10.1 (VIN), U10.3 (CTRL), U11.8 (+Vs); also elsewhere on the board

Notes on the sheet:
Miscelaneous
interrupt config: OD, should be pulled up
1V8, <3mA
3V1-5V, <120mA
Pulse Oximeter & Heart Rate Monitor
Temperature Sensor
1V7-5V5, <85µA
(GND)
(BATT+)
Extension Connector
(VDD)

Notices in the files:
wearable-v2/pcb-expansion-feedback/pcb-expansion-feedback.kicad_pcb:
CERN-OHL-P-2
wearable/pcb/wearable-core.kicad_sch:
© 2021-2023 Herald Project Contributors
Licensed under CERN-OHL-P version 2
wearable/pcb/wearable.kicad_pcb:
© 2021 Herald Project Contributors
© 2021 Herald
